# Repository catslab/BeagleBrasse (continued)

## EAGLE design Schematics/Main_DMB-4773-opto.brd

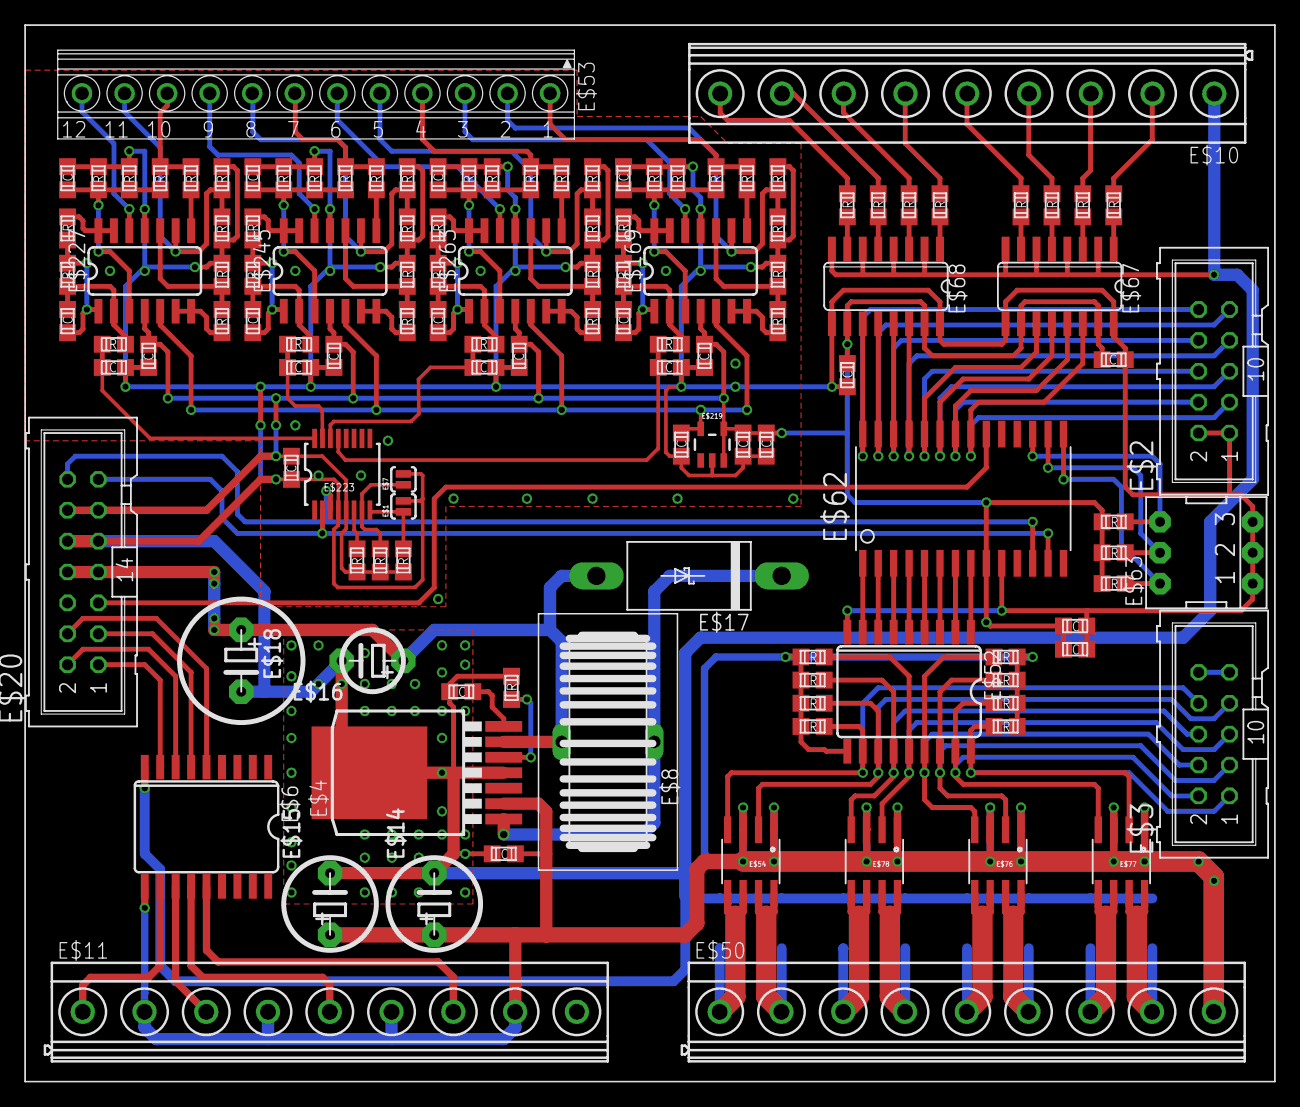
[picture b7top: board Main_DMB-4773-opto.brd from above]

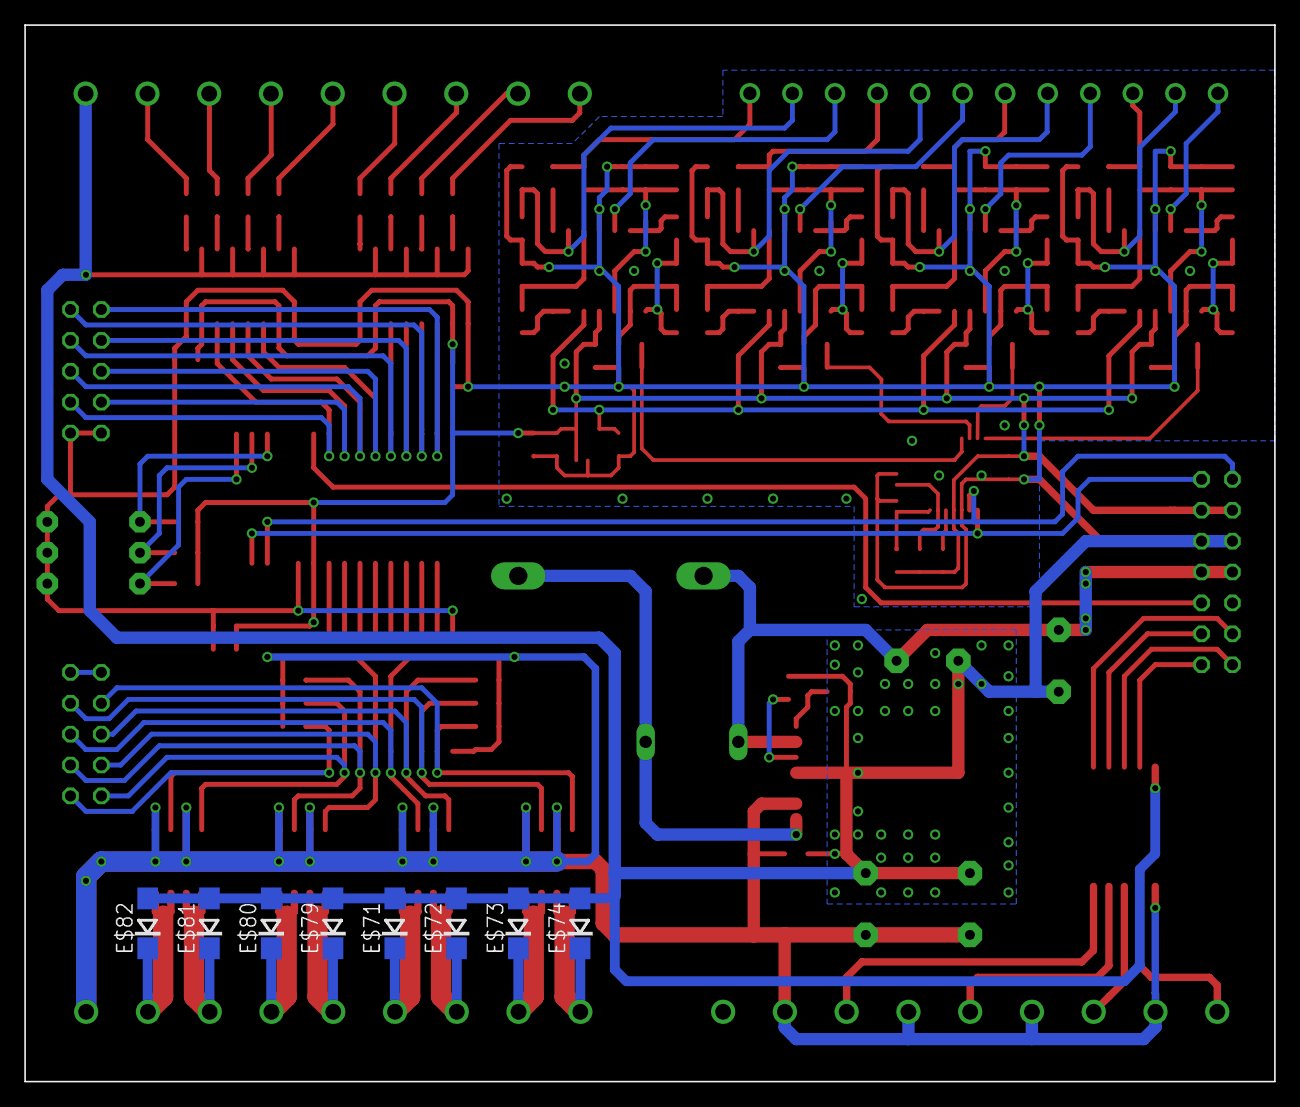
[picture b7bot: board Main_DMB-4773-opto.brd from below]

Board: 2 copper layers, 102.8 x 86.9 mm, 133 parts (8 on the bottom side), 118 nets.

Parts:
E$1, E$7: SJ_2S-NO
E$2, E$3: ML10
E$4: LM2673; DDPACK-7
E$5, E$9, E$13, E$69, E$83, E$84: 100n; C0805
E$6, E$52: ULN2803; SO18L
E$8: KM3.0
E$10, E$11, E$50: MKDSN1,5/9-5,08
E$12, E$49, E$55, E$56, E$57, E$58, E$59, E$60, E$61, E$64, E$65, E$66, E$224, E$225, E$226: 10K; R0805
E$14, E$15: CE02D
E$16: CE02C
E$17: DO201T15
E$18: CE02A
E$20: ML14
E$53: 175317
E$54, E$76, E$77, E$78: SOIC8
E$62: MCP23017; SO28-3
E$63: EPG-03-SMALL
E$67, E$68: ACSL-6400; SO16
E$70: 1u; C0805
E$71, E$72, E$73, E$74, E$79, E$80, E$81, E$82: DO214AC
E$85, E$86, E$87, E$88, E$89, E$90, E$91, E$92: 1.30K; R0805
E$169, E$227, E$245, E$263: SOIC-14
E$170, E$175, E$184, E$185, E$220, E$221, E$228, E$233, E$243, E$246, E$251, E$261, E$264, E$269, E$279: 0.1; C0805
E$171, E$179, E$229, E$237, E$247, E$255, E$265, E$273: 1K; R0805
E$172, E$173, E$230, E$231, E$248, E$249, E$266, E$267: 2K; R0805
E$174, E$178, E$232, E$236, E$250, E$254, E$268, E$272: 39.2K; R0805
E$176, E$234, E$252, E$270: 1.91K; R0805
E$177, E$235, E$253, E$271: 100; R0805
E$180, E$238, E$256, E$274: 26.7K; R0805
E$181, E$239, E$257, E$275: 1.1K; R0805
E$182, E$240, E$258, E$276: 4.7n; C0805
E$183, E$241, E$259, E$277: 51; R0805
E$219: SOT23-5
E$223: AD5316R; TSSOP16

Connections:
+5V: E$4.6, E$8.2, E$16.+, E$17.A, E$18.+, E$20.7, E$20.8
GND: E$1.2, E$2.1, E$2.2, E$4.4, E$4.P$1, E$5.1, E$6.9, E$7.2, E$9.2, E$10.1, E$12.2, E$13.1, E$14.-, E$15.-, E$16.-, E$18.-, E$20.9, E$20.10, E$52.9, E$62.10, E$63.1, E$63.2, E$63.3, E$67.2, E$67.4, E$67.6, E$67.8, E$67.9, E$67.16, E$68.2, E$68.4, E$68.6, E$68.8, E$68.9, E$68.16, E$69.2, E$70.2, E$71.A, E$72.A, E$73.A, E$74.A, E$79.A, E$80.A, E$81.A, E$82.A, E$83.1, E$84.1, E$169.11, E$173.1, E$174.1, E$175.2, E$176.1, E$177.2, E$181.2, E$182.1, E$184.1, E$185.2, E$219.2, E$220.1, E$221.1, E$223.4, E$227.11, E$231.1, E$232.1, E$233.2, E$234.1, E$235.2, E$239.2, E$240.1, E$243.2, E$245.11, E$249.1, E$250.1, E$251.2, E$252.1, E$253.2, E$257.2, E$258.1, E$261.2, E$263.11, E$267.1, E$268.1, E$269.2, E$270.1, E$271.2, E$275.2, E$276.1, E$279.2
S$8: E$10.9, E$85.2
S$11: E$53.1, E$171.1, E$172.1
S$26: E$6.11, E$11.1
S$27: E$6.12, E$11.3
S$28: E$6.13, E$11.5
S$29: E$6.14, E$11.7
S$34: E$1.1, E$223.8, E$224.1
S$35: E$6.6, E$20.3
S$36: E$6.5, E$20.4
S$37: E$6.7, E$20.2
S$38: E$6.8, E$20.1
S$39: E$10.8, E$86.2
S$40: E$10.7, E$87.2
S$41: E$10.6, E$88.2
S$42: E$10.5, E$89.2
S$43: E$10.4, E$90.2
S$44: E$10.3, E$91.2
S$45: E$10.2, E$92.2
S$46: E$68.7, E$85.1
S$81: E$4.2, E$6.10, E$11.2, E$11.4, E$11.6, E$11.8, E$13.2, E$14.+, E$15.+, E$49.1, E$50.9, E$52.10, E$54.1, E$54.3, E$55.1, E$56.1, E$57.1, E$58.2, E$59.2, E$60.2, E$61.2, E$76.1, E$76.3, E$77.1, E$77.3, E$78.1, E$78.3
S$82: E$4.1, E$8.1, E$17.C
S$83: E$4.7, E$5.2
S$85: E$4.5, E$12.1
S$99: E$169.8, E$171.2
S$102: E$169.6, E$169.7, E$180.2
S$105: E$53.2, E$169.9, E$176.2, E$177.1
S$108: E$169.1, E$170.1, E$178.1, E$179.1
S$114: E$169.2, E$170.2, E$178.2, E$183.1
S$120: E$169.13, E$169.14, E$179.2
S$126: E$169.10, E$180.1, E$181.1
S$132: E$169.3, E$172.2, E$173.2, E$174.2, E$175.1
S$133: E$53.3, E$169.12
S$134: E$182.2, E$183.2, E$223.13
S$145: E$3.9, E$3.10
S$151: E$169.5, E$184.2, E$219.5, E$227.5, E$245.5, E$263.5
S$152: E$3.8, E$49.2, E$52.11, E$54.4
S$153: E$3.7, E$52.12, E$54.2, E$55.2
S$158: E$3.6, E$52.13, E$56.2, E$78.4
S$159: E$3.5, E$52.14, E$57.2, E$78.2
S$160: E$3.4, E$52.15, E$58.1, E$76.4
S$162: E$3.3, E$52.16, E$59.1, E$76.2
S$163: E$3.2, E$52.17, E$60.1, E$77.4
S$164: E$3.1, E$52.18, E$61.1, E$77.2
S$166: E$52.8, E$62.1
S$167: E$52.7, E$62.2
S$168: E$52.6, E$62.3
S$169: E$52.5, E$62.4
S$170: E$52.4, E$62.5
S$171: E$52.3, E$62.6
S$172: E$52.2, E$62.7
S$173: E$52.1, E$62.8
S$182: E$2.10, E$62.28, E$68.11
S$183: E$2.9, E$62.27, E$68.12
S$184: E$2.8, E$62.26, E$68.13
S$185: E$2.7, E$62.25, E$68.14
S$186: E$2.6, E$62.24, E$67.11
S$187: E$2.5, E$62.23, E$67.12
S$188: E$2.4, E$62.22, E$67.13
S$189: E$2.3, E$62.21, E$67.14
S$190: E$20.5, E$62.20
S$191: E$62.17, E$63.4, E$65.2
S$192: E$62.16, E$63.5, E$64.2
S$193: E$62.15, E$63.6, E$66.2
S$194: E$50.1, E$54.5, E$54.6, E$74.C
S$195: E$53.19, E$229.1, E$230.1
S$196: E$227.8, E$229.2
S$197: E$227.6, E$227.7, E$238.2
S$198: E$53.20, E$227.9, E$234.2, E$235.1
S$199: E$227.1, E$228.1, E$236.1, E$237.1
S$200: E$227.2, E$228.2, E$236.2, E$241.1
S$201: E$227.13, E$227.14, E$237.2
S$202: E$227.10, E$238.1, E$239.1
S$203: E$50.2, E$54.7, E$54.8, E$73.C
S$204: E$227.3, E$230.2, E$231.2, E$232.2, E$233.1
S$205: E$53.21, E$227.12
S$206: E$223.16, E$240.2, E$241.2
S$207: E$50.5, E$76.5, E$76.6, E$79.C
S$208: E$50.6, E$76.7, E$76.8, E$80.C
S$209: E$53.7, E$247.1, E$248.1
S$210: E$245.8, E$247.2
S$211: E$245.6, E$245.7, E$256.2
S$212: E$53.8, E$245.9, E$252.2, E$253.1
S$213: E$245.1, E$246.1, E$254.1, E$255.1
S$214: E$245.2, E$246.2, E$254.2, E$259.1
S$215: E$245.13, E$245.14, E$255.2
S$216: E$245.10, E$256.1, E$257.1
S$217: E$50.7, E$77.5, E$77.6, E$81.C
S$218: E$245.3, E$248.2, E$249.2, E$250.2, E$251.1
S$219: E$53.9, E$245.12
S$220: E$223.15, E$258.2, E$259.2
S$221: E$50.8, E$77.7, E$77.8, E$82.C
S$222: E$50.3, E$72.C, E$78.5, E$78.6
S$223: E$53.4, E$265.1, E$266.1
S$224: E$263.8, E$265.2
S$225: E$263.6, E$263.7, E$274.2
S$226: E$53.5, E$263.9, E$270.2, E$271.1
S$227: E$263.1, E$264.1, E$272.1, E$273.1
S$228: E$263.2, E$264.2, E$272.2, E$277.1
S$229: E$263.13, E$263.14, E$273.2
S$230: E$263.10, E$274.1, E$275.1
S$231: E$223.6, E$226.1
S$232: E$263.3, E$266.2, E$267.2, E$268.2, E$269.1
S$233: E$53.6, E$263.12
S$234: E$223.14, E$276.2, E$277.2
S$235: E$7.1, E$223.7, E$225.1
S$236: E$50.4, E$71.C, E$78.7, E$78.8
S$240: E$68.5, E$86.1
S$241: E$68.3, E$87.1
S$242: E$68.1, E$88.1
S$243: E$67.7, E$89.1
S$244: E$67.5, E$90.1
S$245: E$67.3, E$91.1
S$246: E$67.1, E$92.1
SCL: E$20.14, E$62.12, E$223.3
SDA: E$20.13, E$62.13, E$223.2
VCC: E$9.1, E$20.11, E$20.12, E$62.9, E$64.1, E$65.1, E$66.1, E$67.10, E$67.15, E$68.10, E$68.15, E$69.1, E$70.1, E$83.2, E$84.2, E$169.4, E$185.1, E$219.3, E$219.4, E$220.2, E$221.2, E$223.5, E$224.2, E$225.2, E$226.2, E$227.4, E$243.1, E$245.4, E$261.1, E$263.4, E$279.1

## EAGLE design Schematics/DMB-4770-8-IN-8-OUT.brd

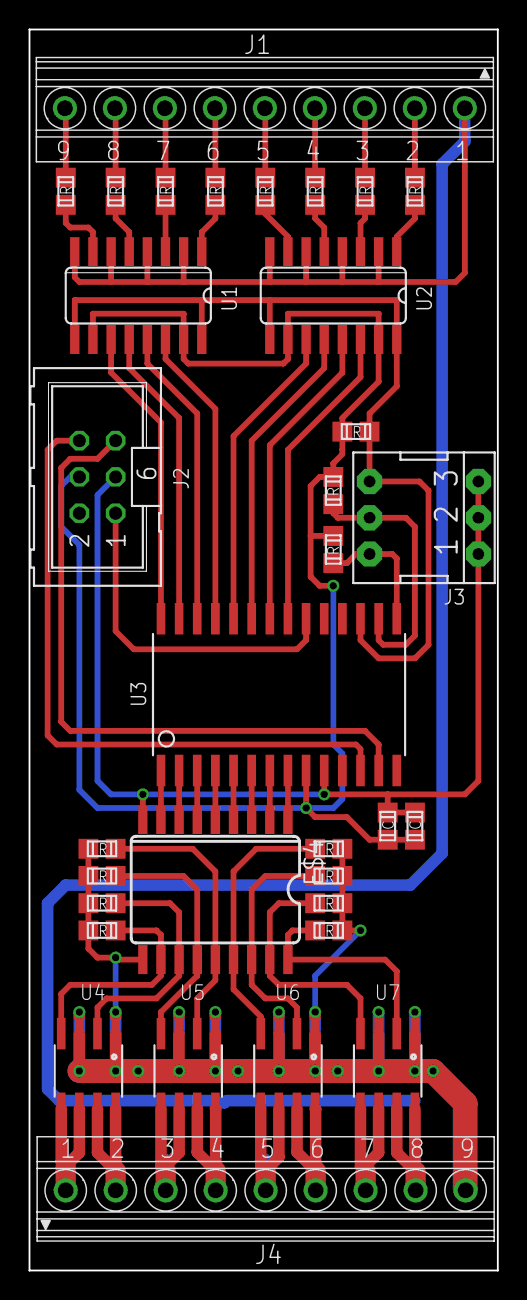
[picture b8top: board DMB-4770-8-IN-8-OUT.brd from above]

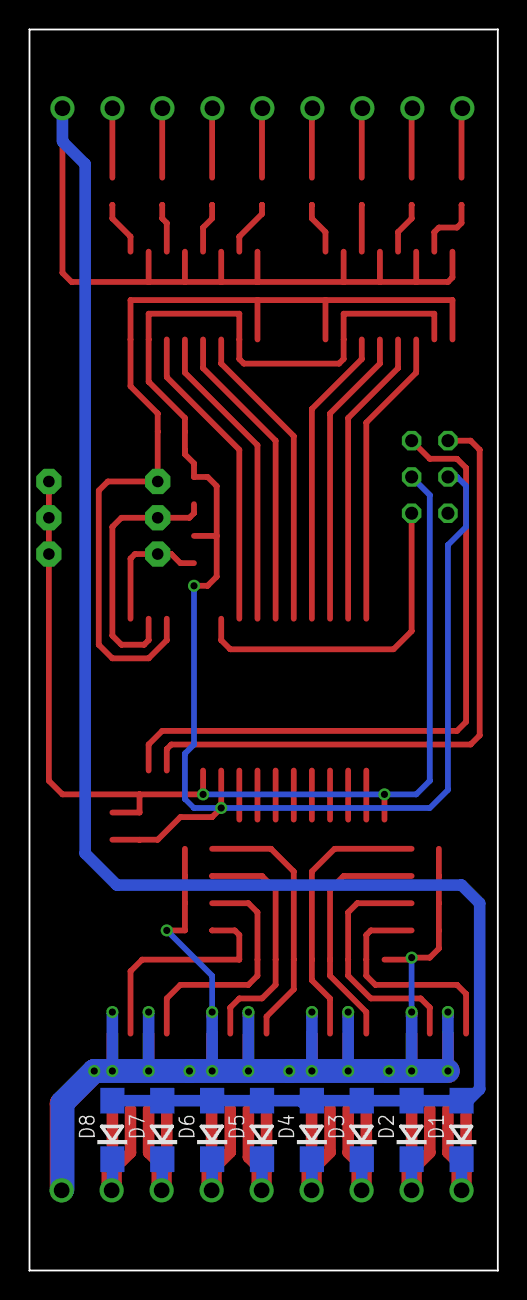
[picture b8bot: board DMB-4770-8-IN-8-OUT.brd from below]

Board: 2 copper layers, 32.8 x 86.9 mm, 41 parts (8 on the bottom side), 58 nets.

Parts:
C1: 100n; C0805
C2: 1u; C0805
D1, D2, D3, D4, D5, D6, D7, D8: DO214AC
E$4: ULN2803; SO18L
J1, J4: 1751316
J2: ML6
J3: EPG-03-SMALL
R1, R2, R3, R4, R5, R6, R7, R8: 1.30K; R0805
R9, R10, R11, R12, R13, R14, R15, R16, R17, R18, R19: 10K; R0805
U1, U2: ACSL-6400; SO16
U3: SO28-3
U4, U5, U6, U7: SOIC8

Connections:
3V3: C1.1, C2.1, J2.4, R9.1, R10.1, R11.1, U1.10, U1.15, U2.10, U2.15, U3.9
GND: J3.4, R9.2, U1.9, U1.16, U2.9, U2.16, U3.17
POWER_GND: D1.A, D2.A, D3.A, D4.A, D5.A, D6.A, D7.A, D8.A, J1.1, U1.2, U1.4, U1.6, U1.8, U2.2, U2.4, U2.6, U2.8
S$8: D1.C, J4.1, U4.5, U4.6
S$9: D2.C, J4.2, U4.7, U4.8
S$10: D3.C, J4.3, U5.5, U5.6
S$11: D4.C, J4.4, U5.7, U5.8
S$13: D5.C, J4.5, U6.5, U6.6
S$14: D6.C, J4.6, U6.7, U6.8
S$15: D7.C, J4.7, U7.5, U7.6
S$16: D8.C, J4.8, U7.7, U7.8
S$20: E$4.11, R15.2, U4.4
S$21: E$4.12, R14.2, U4.2
S$23: E$4.13, R13.2, U5.4
S$25: E$4.14, R12.2, U5.2
S$28: E$4.15, R16.1, U6.4
S$29: E$4.16, R17.1, U6.2
S$31: E$4.17, R18.1, U7.4
S$32: E$4.18, R19.1, U7.2
S$33: E$4.8, U3.1
S$34: E$4.7, U3.2
S$35: E$4.6, U3.3
S$38: E$4.5, U3.4
S$39: E$4.4, U3.5
S$40: E$4.3, U3.6
S$41: E$4.2, U3.7
S$42: E$4.1, U3.8
S$47: R8.1, U2.1
S$48: J2.6, U3.12
S$49: J2.5, U3.13
S$50: C1.2, C2.2, E$4.9, J2.3, J3.1, J3.2, J3.3, U3.10
S$55: R7.1, U2.3
S$59: J2.1, U3.20
S$66: J3.6, R11.2, U3.15
S$67: J3.5, R10.2, U3.16
S$71: R6.1, U2.5
S$72: R5.1, U2.7
S$73: R4.1, U1.1
S$74: R3.1, U1.3
S$75: R2.1, U1.5
S$76: R1.1, U1.7
S$77: J1.9, R1.2
S$78: J1.8, R2.2
S$79: J1.7, R3.2
S$80: J1.6, R4.2
S$81: J1.5, R5.2
S$82: J1.4, R6.2
S$83: J1.3, R7.2
S$84: J1.2, R8.2
S$89: U1.11, U3.28
S$90: U1.12, U3.27
S$91: U1.13, U3.26
S$92: U1.14, U3.25
S$93: U2.11, U3.24
S$94: U2.12, U3.23
S$95: U2.13, U3.22
S$96: U2.14, U3.21
VCOM: E$4.10, J4.9, R12.1, R13.1, R14.1, R15.1, R16.2, R17.2, R18.2, R19.2, U4.1, U4.3, U5.1, U5.3, U6.1, U6.3, U7.1, U7.3

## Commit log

2014-10-16 Schematics v1.0
2014-10-16 Added pdf file
2014-10-19 Modification v0.1
2014-10-20 Ajout carte relais
2014-10-22 Ajout carte 4 entrées et 4 sorties analogiques
2014-10-23 Ajout carte 8 entrées optos et 8 sorties 2A
2014-10-23 Ajout schemas pour carte 4 entrées analog et 4 sorties analog
2014-10-23 Correction schémas pour ajout des diodes de protection
2014-10-25 Correction valeurs
2014-10-25 Ajout dip switch bord de carte
2014-10-28 Correction empreinte MCP23008
2014-10-28 Correction Resistance Sense 0-20mA
2014-10-31 Ajout carte 8in 8out pour boitier 4771
2014-11-08 Modifications et ajout des cartes C
2014-11-09 Ajout cape et modification cartes C
2014-11-09 Ajout panel pour prototypage
2014-11-09 Ajout 1-wire
2014-11-09 Ajout schema cape
2014-11-09 Schema Mainboard opto sans regulateur 5V
2014-11-09 Renomage
2014-11-09 Renommage
2014-12-07 Correction erreur GND
2014-12-08 Modifications plan de masse et routage
2014-12-08 Modification empreintes resistances
    Au lieu de 2 resistances 500, une seule 250 en 1206
2014-12-08 Ajout d'un circuit v2 alim 5V
    Remplacement de l’alimentation 5V
2014-12-08 ajout du .gitignore
2014-12-08 Nettoyage
2018-08-28 Adding new designs
2018-08-28 ajout interface pi pour base phoenix UM
2018-08-28 Finalisation interface PI
